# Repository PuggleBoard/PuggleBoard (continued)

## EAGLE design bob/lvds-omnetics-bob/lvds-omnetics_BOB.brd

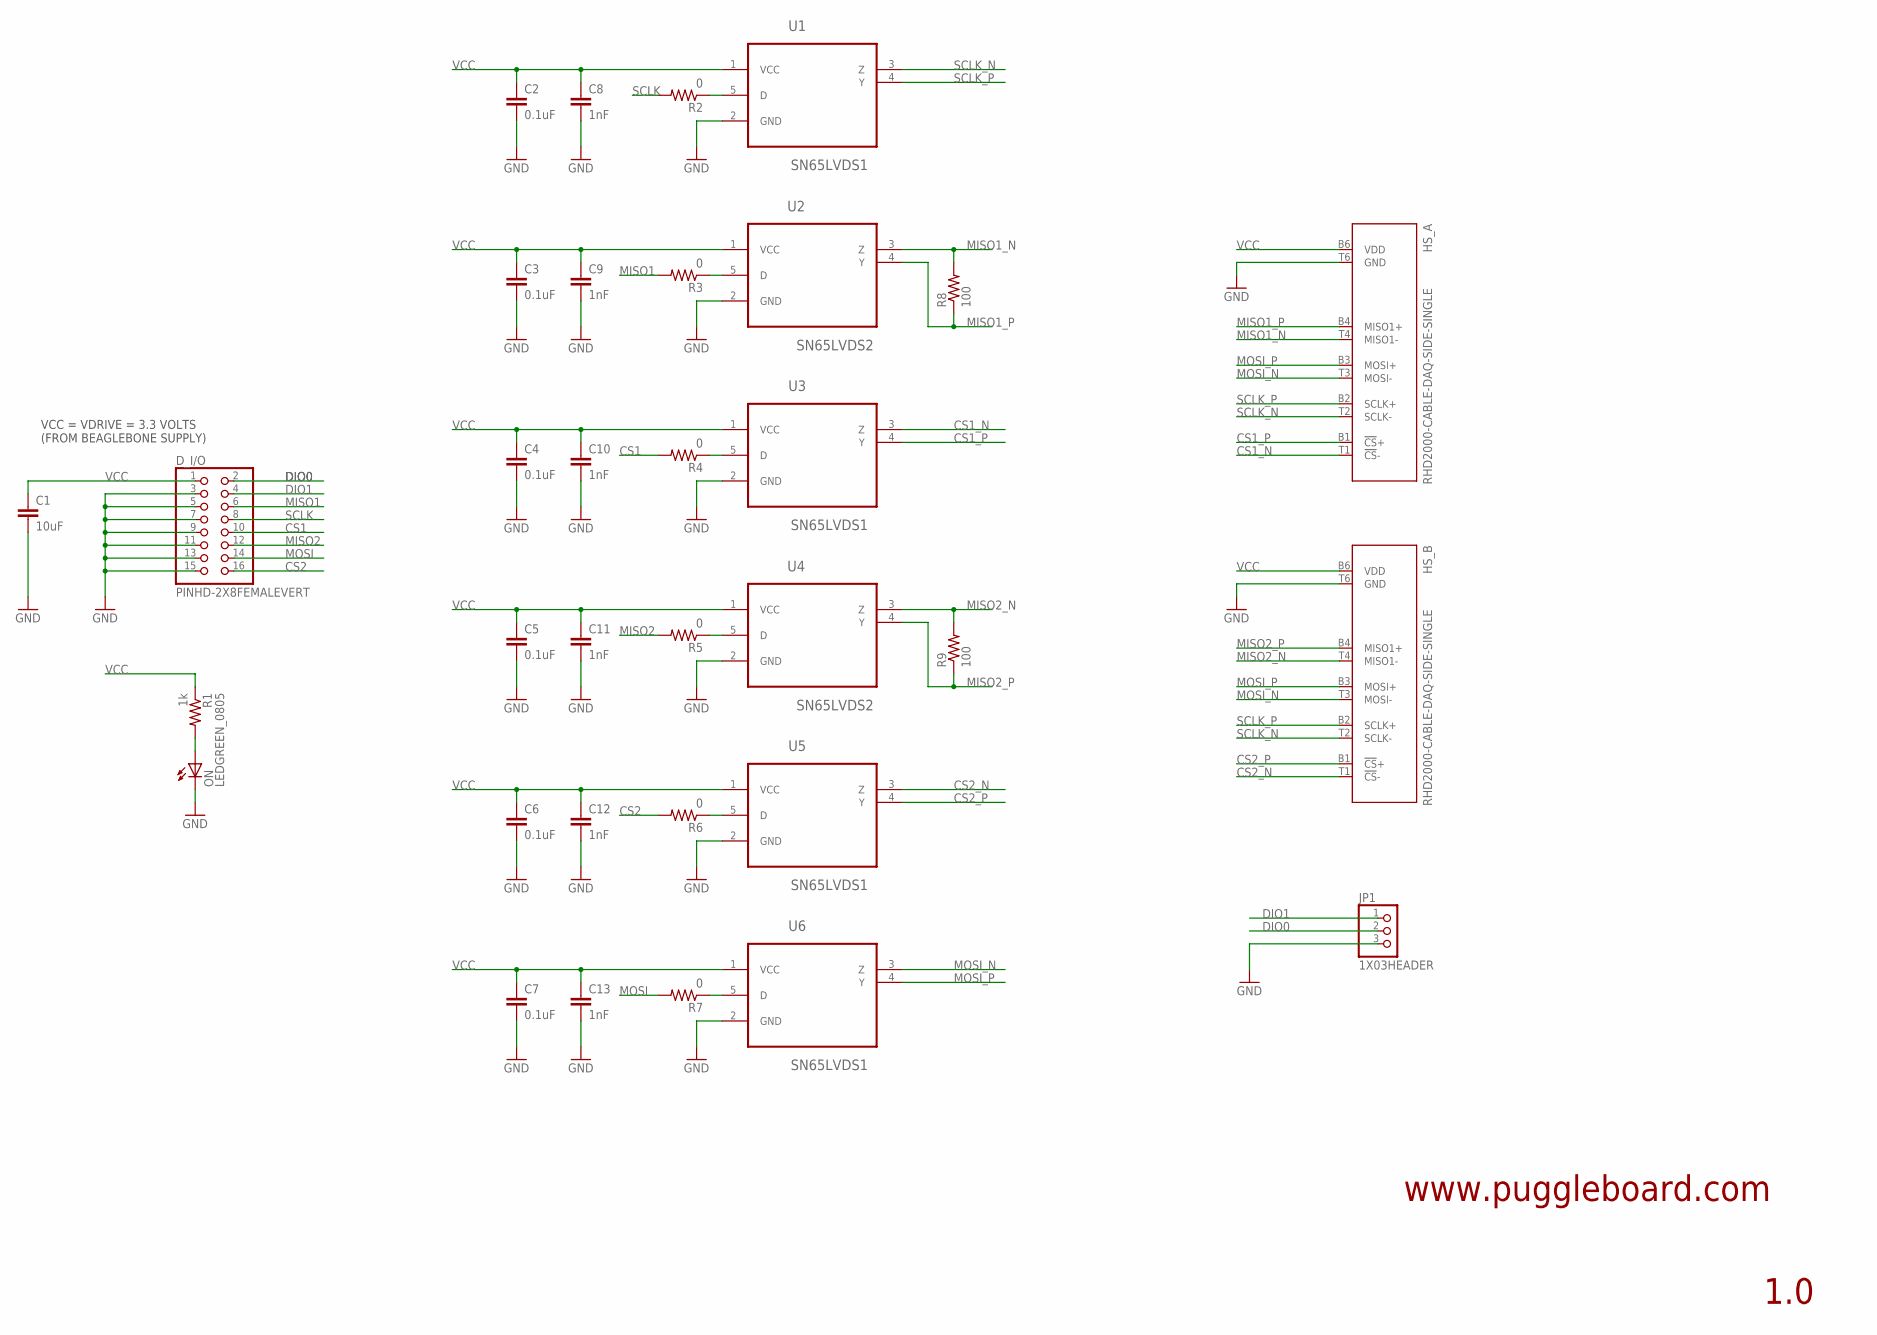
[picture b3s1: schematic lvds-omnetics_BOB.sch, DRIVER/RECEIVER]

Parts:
C1: 10uF; 0805
C2, C3, C4, C5, C6, C7: 0.1uF; 0603
C8, C9, C10, C11, C12, C13: 1nF; 0603
D_I/O: PINHD-2X8FEMALEVERT; 2X08
HS_A: RHD2000-CABLE-DAQ-SIDE-SINGLE; OMNETICS_PZN_12_AA-SINGLEBUS
HS_B: RHD2000-CABLE-DAQ-SIDE-SINGLE; OMNETICS_PZN_12_AA-SINGLEBUS
JP1: 1X03HEADER; 1X03
ON: LEDGREEN_0805; CHIP-LED0805
R1: 1k; 0603
R2, R3, R4, R5, R6, R7: 0; 0603
R8, R9: 100; 0603
U1, U3, U5, U6: SN65LVDS1; SOT95P280X145-5N; DIGIKEY 296-6919-1-ND
U2, U4: SN65LVDS2; SOT95P280X145-5N; DIGIKEY 296-6920-1-ND

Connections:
CS1: D_I/O.10, R4.2
CS1_N: HS_A.T1 (!CS!-), U3.3 (Z)
CS1_P: HS_A.B1 (!CS!+), U3.4 (Y)
CS2: D_I/O.16, R6.2
CS2_N: HS_B.T1 (!CS!-), U5.3 (Z)
CS2_P: HS_B.B1 (!CS!+), U5.4 (Y)
DIO0: D_I/O.2, JP1.2
DIO1: D_I/O.4, JP1.1
GND: C1.2, C2.2, C3.2, C4.2, C5.2, C6.2, C7.2, C8.2, C9.2, C10.2, C11.2, C12.2, C13.2, D_I/O.3, D_I/O.5, D_I/O.7, D_I/O.9, D_I/O.11, D_I/O.13, D_I/O.15, HS_A.T6 (GND), HS_B.T6 (GND), JP1.3, ON.C, U1.2 (GND), U2.2 (GND), U3.2 (GND), U4.2 (GND), U5.2 (GND), U6.2 (GND)
MISO1: D_I/O.6, R3.2
MISO1_N: HS_A.T4 (MISO1-), R8.2, U2.3 (Z)
MISO1_P: HS_A.B4 (MISO1+), R8.1, U2.4 (Y)
MISO2: D_I/O.12, R5.2
MISO2_N: HS_B.T4 (MISO1-), R9.2, U4.3 (Z)
MISO2_P: HS_B.B4 (MISO1+), R9.1, U4.4 (Y)
MOSI: D_I/O.14, R7.2
MOSI_N: HS_A.T3 (MOSI-), HS_B.T3 (MOSI-), U6.3 (Z)
MOSI_P: HS_A.B3 (MOSI+), HS_B.B3 (MOSI+), U6.4 (Y)
unnamed: R3.1, U2.5 (D)
unnamed: R4.1, U3.5 (D)
unnamed: R5.1, U4.5 (D)
unnamed: R6.1, U5.5 (D)
unnamed: R7.1, U6.5 (D)
unnamed: R2.1, U1.5 (D)
unnamed: ON.A, R1.2
SCLK: D_I/O.8, R2.2
SCLK_N: HS_A.T2 (SCLK-), HS_B.T2 (SCLK-), U1.3 (Z)
SCLK_P: HS_A.B2 (SCLK+), HS_B.B2 (SCLK+), U1.4 (Y)
VCC: C1.1, C2.1, C3.1, C4.1, C5.1, C6.1, C7.1, C8.1, C9.1, C10.1, C11.1, C12.1, C13.1, D_I/O.1, HS_A.B6 (VDD), HS_B.B6 (VDD), R1.1, U1.1 (VCC), U2.1 (VCC), U3.1 (VCC), U4.1 (VCC), U5.1 (VCC), U6.1 (VCC)

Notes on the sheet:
www.puggleboard.com
1.0
VCC = VDRIVE = 3.3 VOLTS (FROM BEAGLEBONE SUPPLY)

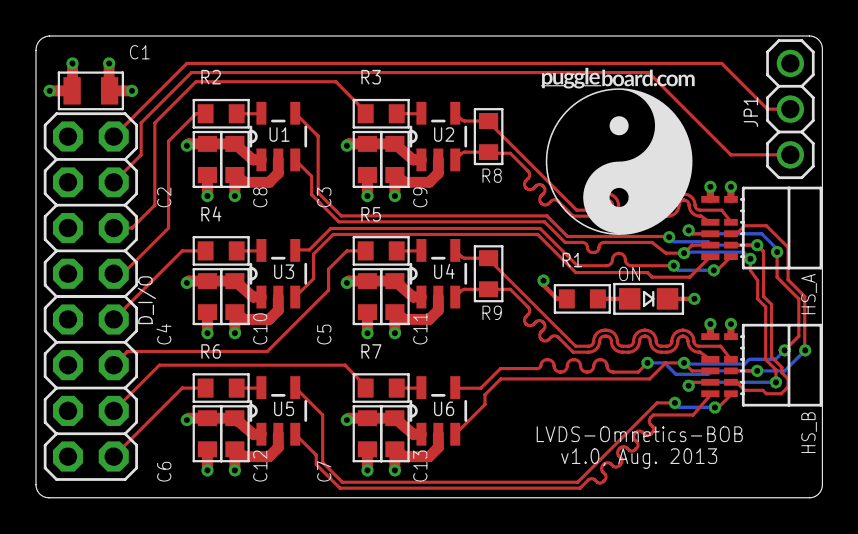
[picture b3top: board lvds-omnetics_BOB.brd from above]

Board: 4 copper layers, 43.7 x 25.7 mm, 35 parts (1 on the bottom side), 29 nets.

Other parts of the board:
U$1: PB-LOGO
U$2: OSHW_FILLX500_NOTEXT

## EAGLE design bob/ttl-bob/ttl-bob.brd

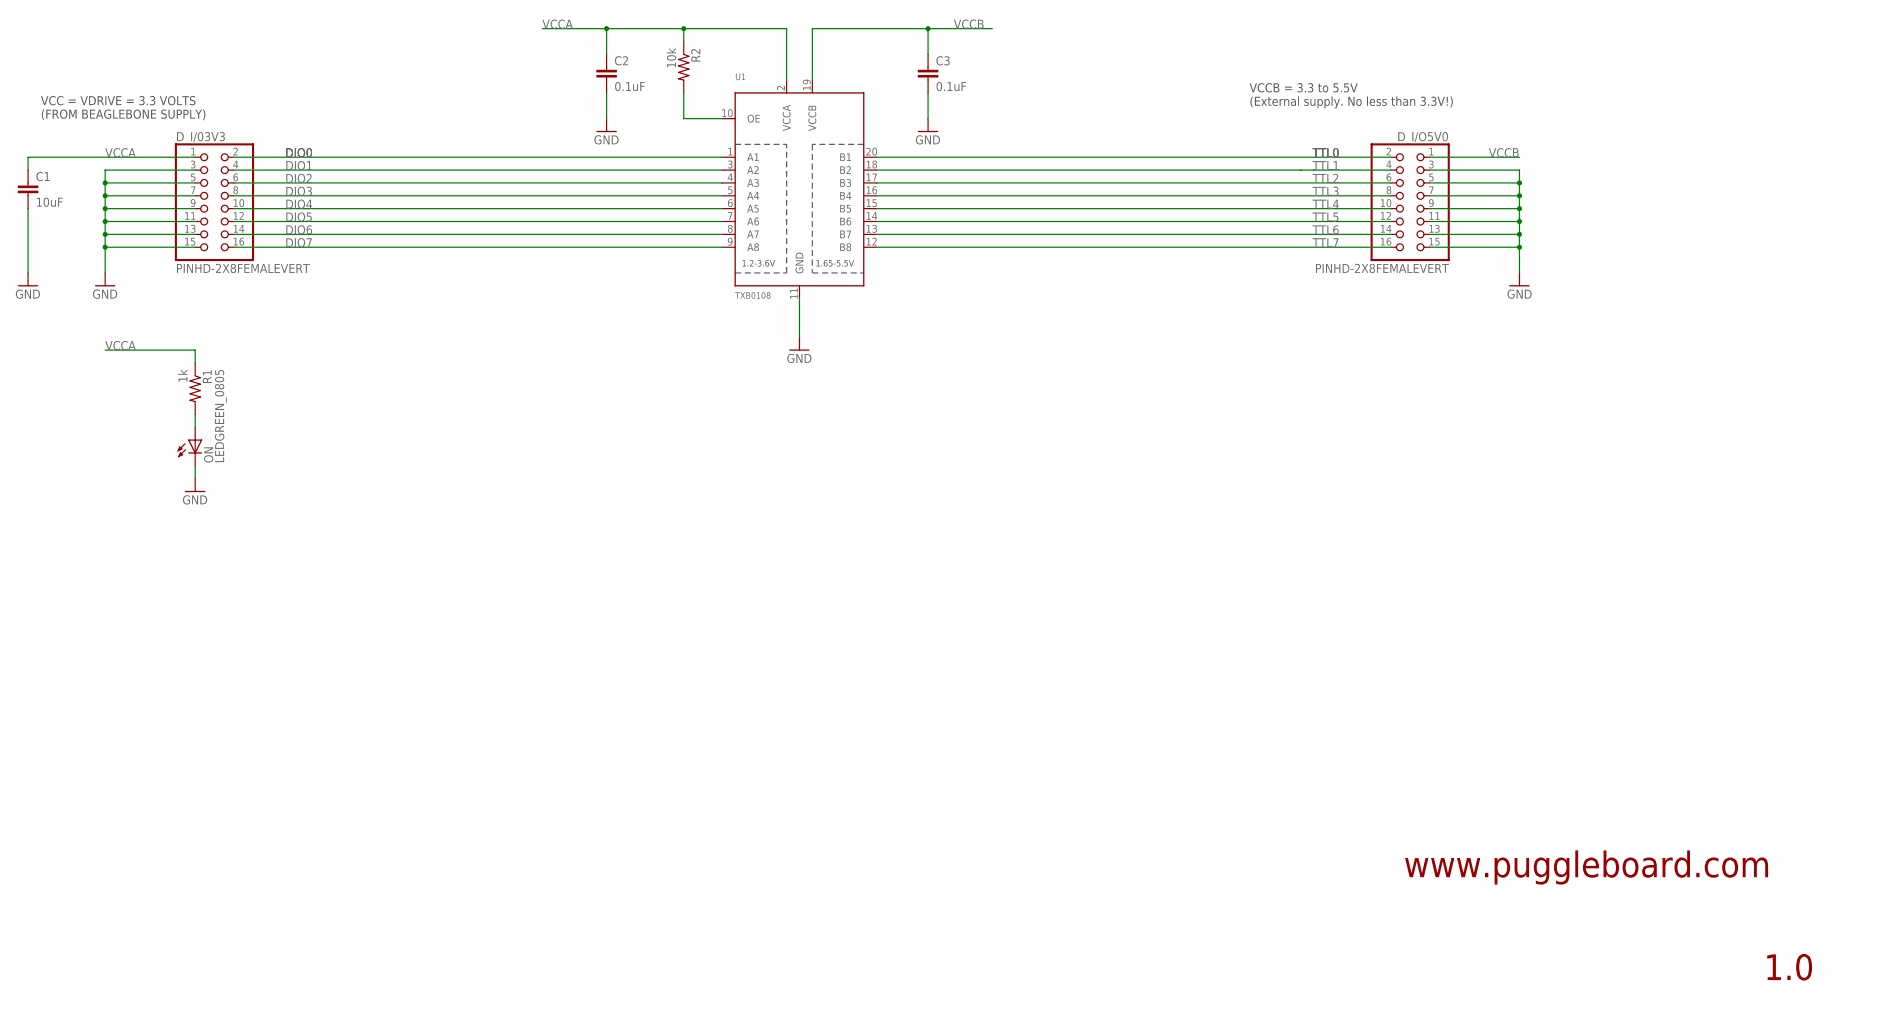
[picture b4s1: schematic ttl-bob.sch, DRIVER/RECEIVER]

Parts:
C1: 10uF; 0805
C2, C3: 0.1uF; 0603
D_I/03V3: PINHD-2X8FEMALEVERT; 2X08
D_I/O5V0: PINHD-2X8FEMALEVERT; 2X08
ON: LEDGREEN_0805; CHIP-LED0805
R1: 1k; 0603; MPN ERJ-3EKF1001V
R2: 10k; 0603; MPN ERJ-3EKF1002V
U1: TXB0108; TSSOP20

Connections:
DIO0: D_I/03V3.2, U1.1 (A1)
DIO1: D_I/03V3.4, U1.3 (A2)
DIO2: D_I/03V3.6, U1.4 (A3)
DIO3: D_I/03V3.8, U1.5 (A4)
DIO4: D_I/03V3.10, U1.6 (A5)
DIO5: D_I/03V3.12, U1.7 (A6)
DIO6: D_I/03V3.14, U1.8 (A7)
DIO7: D_I/03V3.16, U1.9 (A8)
GND: C1.2, C2.2, C3.2, D_I/03V3.3, D_I/03V3.5, D_I/03V3.7, D_I/03V3.9, D_I/03V3.11, D_I/03V3.13, D_I/03V3.15, D_I/O5V0.3, D_I/O5V0.5, D_I/O5V0.7, D_I/O5V0.9, D_I/O5V0.11, D_I/O5V0.13, D_I/O5V0.15, ON.C, U1.11 (GND)
unnamed: R2.2, U1.10 (OE)
unnamed: ON.A, R1.2
TTL0: D_I/O5V0.2, U1.20 (B1)
TTL1: D_I/O5V0.4, U1.18 (B2)
TTL2: D_I/O5V0.6, U1.17 (B3)
TTL3: D_I/O5V0.8, U1.16 (B4)
TTL4: D_I/O5V0.10, U1.15 (B5)
TTL5: D_I/O5V0.12, U1.14 (B6)
TTL6: D_I/O5V0.14, U1.13 (B7)
TTL7: D_I/O5V0.16, U1.12 (B8)
VCCA: C1.1, C2.1, D_I/03V3.1, R1.1, R2.1, U1.2 (VCCA)
VCCB: C3.1, D_I/O5V0.1, U1.19 (VCCB)

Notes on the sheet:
www.puggleboard.com
1.0
VCC = VDRIVE = 3.3 VOLTS (FROM BEAGLEBONE SUPPLY)
VCCB = 3.3 to 5.5V (External supply. No less than 3.3V!)

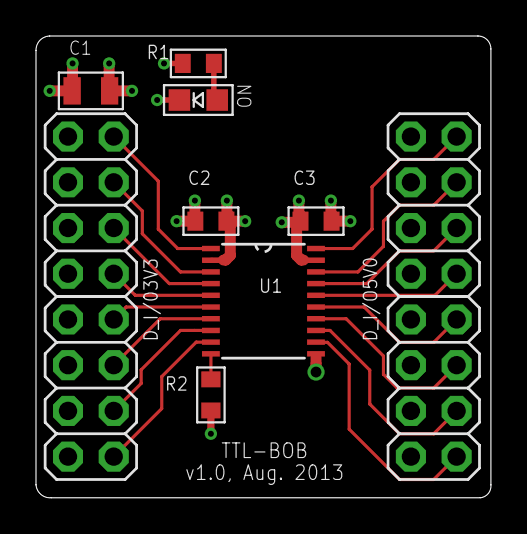
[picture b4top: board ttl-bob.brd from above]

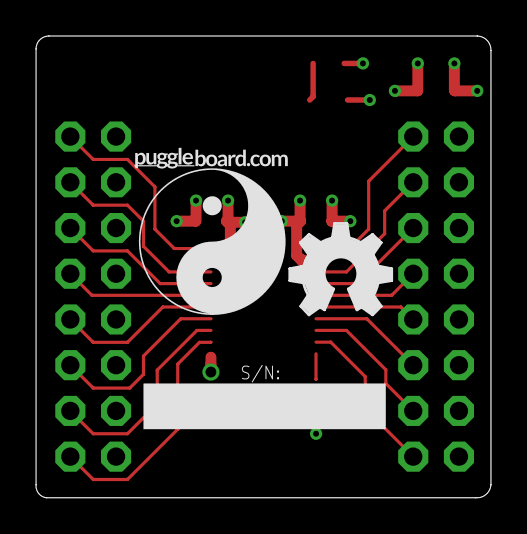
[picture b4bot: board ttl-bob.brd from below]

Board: 4 copper layers, 25.3 x 25.7 mm, 11 parts (2 on the bottom side), 21 nets.

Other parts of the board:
U$1: PB-LOGO
U$2: OSHW_FILLX200_NOTEXT

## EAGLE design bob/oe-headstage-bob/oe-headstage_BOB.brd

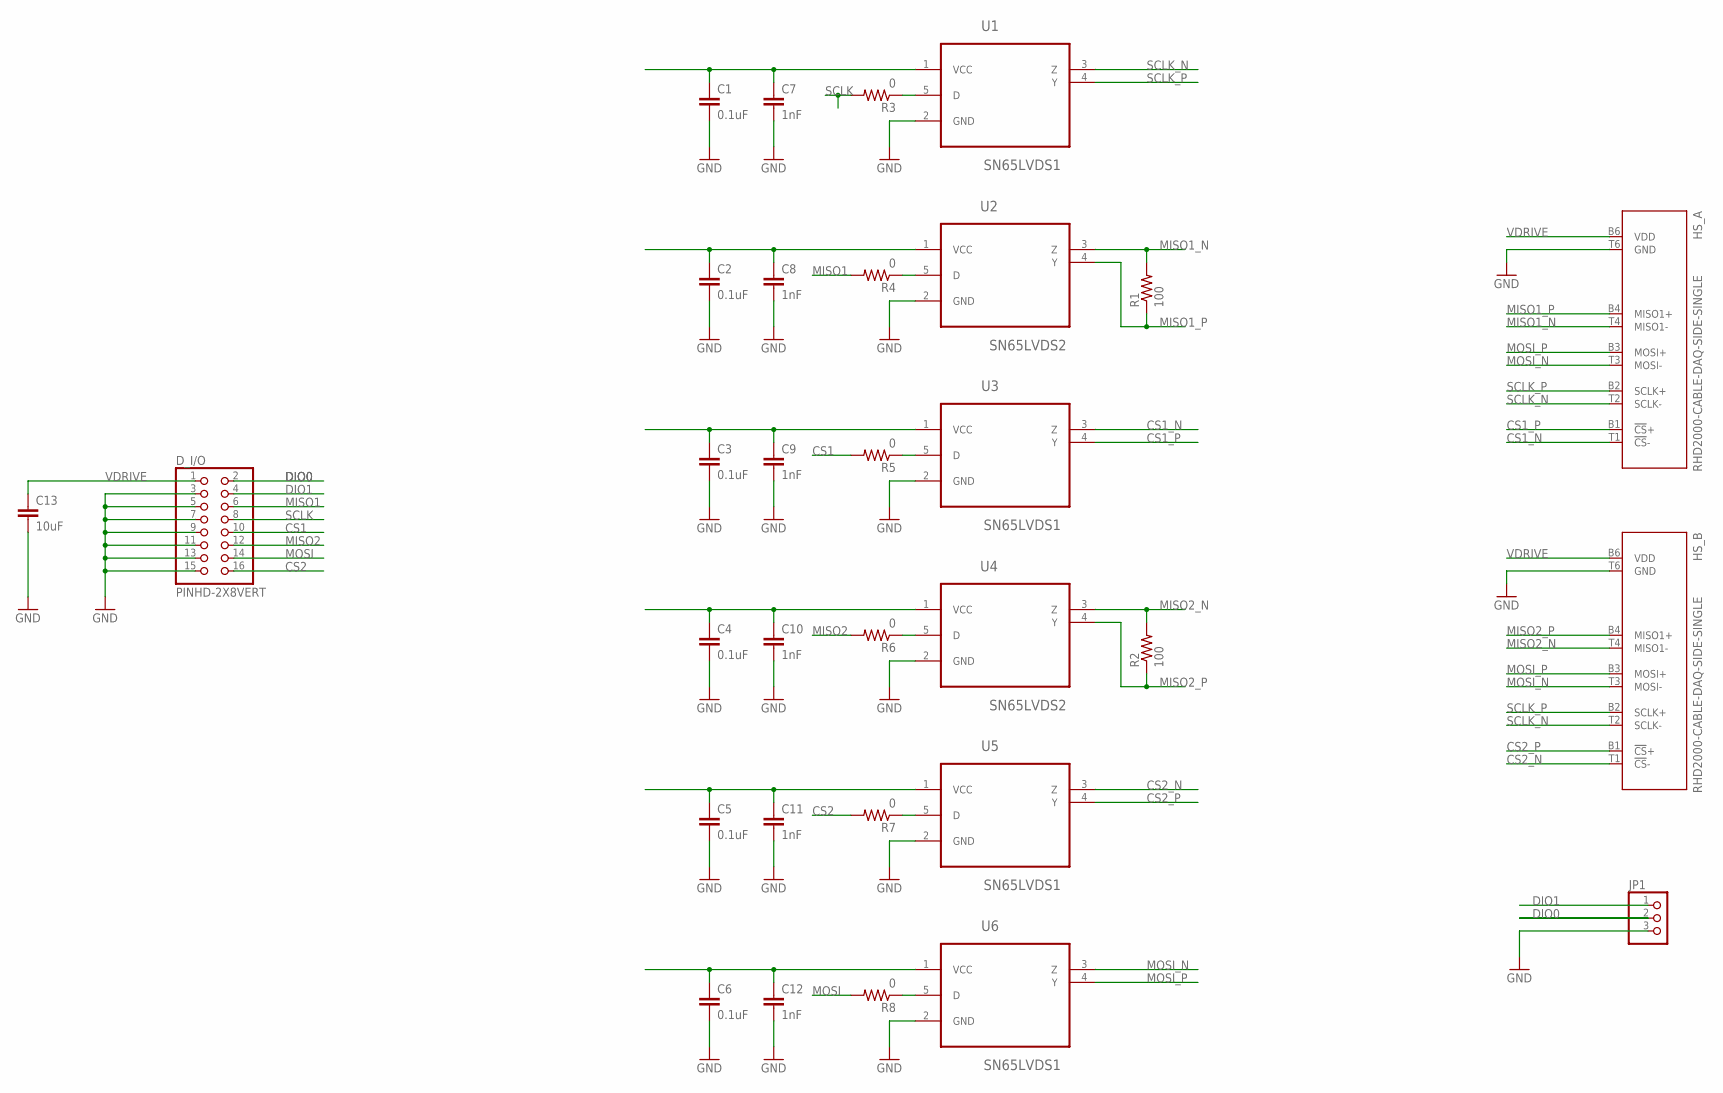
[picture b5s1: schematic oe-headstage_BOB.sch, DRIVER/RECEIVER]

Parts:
C1, C2, C3, C4, C5, C6: 0.1uF; 0603
C7, C8, C9, C10, C11, C12: 1nF; 0603
C13: 10uF; 0805
D_I/O: PINHD-2X8VERT; 2X08
HS_A: RHD2000-CABLE-DAQ-SIDE-SINGLE; OMNETICS_PZN_12_AA-SINGLEBUS
HS_B: RHD2000-CABLE-DAQ-SIDE-SINGLE; OMNETICS_PZN_12_AA-SINGLEBUS
JP1: PINHD-1X3; 1X03
R1, R2: 100; 0603
R3, R4, R5, R6, R7, R8: 0; 0603
U1, U3, U5, U6: SN65LVDS1; SOT95P280X145-5N; DIGIKEY 296-6919-1-ND
U2, U4: SN65LVDS2; SOT95P280X145-5N; DIGIKEY 296-6920-1-ND

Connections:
CS1: D_I/O.10, R5.2
CS1_N: HS_A.T1 (!CS!-), U3.3 (Z)
CS1_P: HS_A.B1 (!CS!+), U3.4 (Y)
CS2: D_I/O.16, R7.2
CS2_N: HS_B.T1 (!CS!-), U5.3 (Z)
CS2_P: HS_B.B1 (!CS!+), U5.4 (Y)
DIO0: D_I/O.2, JP1.2
DIO1: D_I/O.4, JP1.1
GND: C1.2, C2.2, C3.2, C4.2, C5.2, C6.2, C7.2, C8.2, C9.2, C10.2, C11.2, C12.2, C13.2, D_I/O.3, D_I/O.5, D_I/O.7, D_I/O.9, D_I/O.11, D_I/O.13, D_I/O.15, HS_A.T6 (GND), HS_B.T6 (GND), JP1.3, U1.2 (GND), U2.2 (GND), U3.2 (GND), U4.2 (GND), U5.2 (GND), U6.2 (GND)
MISO1: D_I/O.6, R4.2
MISO1_N: HS_A.T4 (MISO1-), R1.2, U2.3 (Z)
MISO1_P: HS_A.B4 (MISO1+), R1.1, U2.4 (Y)
MISO2: D_I/O.12, R6.2
MISO2_N: HS_B.T4 (MISO1-), R2.2, U4.3 (Z)
MISO2_P: HS_B.B4 (MISO1+), R2.1, U4.4 (Y)
MOSI: D_I/O.14, R8.2
MOSI_N: HS_A.T3 (MOSI-), HS_B.T3 (MOSI-), U6.3 (Z)
MOSI_P: HS_A.B3 (MOSI+), HS_B.B3 (MOSI+), U6.4 (Y)
unnamed: R4.1, U2.5 (D)
unnamed: R5.1, U3.5 (D)
unnamed: R6.1, U4.5 (D)
unnamed: R7.1, U5.5 (D)
unnamed: R8.1, U6.5 (D)
unnamed: R3.1, U1.5 (D)
SCLK: D_I/O.8, R3.2
SCLK_N: HS_A.T2 (SCLK-), HS_B.T2 (SCLK-), U1.3 (Z)
SCLK_P: HS_A.B2 (SCLK+), HS_B.B2 (SCLK+), U1.4 (Y)
VDRIVE: C1.1, C2.1, C3.1, C4.1, C5.1, C6.1, C7.1, C8.1, C9.1, C10.1, C11.1, C12.1, C13.1, D_I/O.1, HS_A.B6 (VDD), HS_B.B6 (VDD), U1.1 (VCC), U2.1 (VCC), U3.1 (VCC), U4.1 (VCC), U5.1 (VCC), U6.1 (VCC)

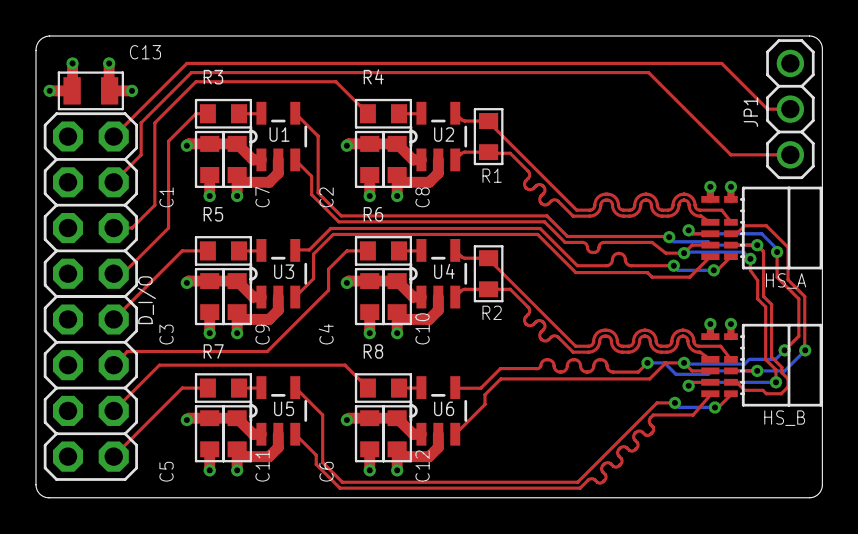
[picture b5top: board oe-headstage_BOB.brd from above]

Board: 4 copper layers, 43.7 x 25.7 mm, 31 parts (0 on the bottom side), 28 nets.

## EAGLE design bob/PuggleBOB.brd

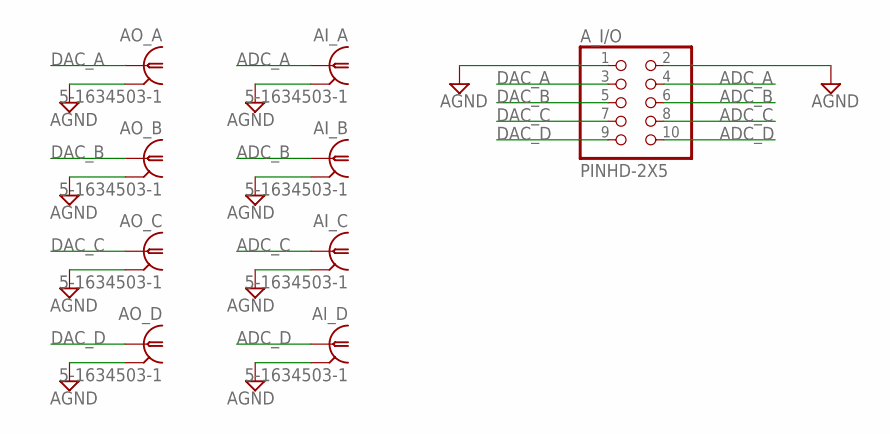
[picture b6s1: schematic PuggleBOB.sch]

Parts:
AI_A: 5-1634503-1; B35N61
AI_B: 5-1634503-1; B35N61
AI_C: 5-1634503-1; B35N61
AI_D: 5-1634503-1; B35N61
AO_A: 5-1634503-1; B35N61
AO_B: 5-1634503-1; B35N61
AO_C: 5-1634503-1; B35N61
AO_D: 5-1634503-1; B35N61
A_I/O: PINHD-2X5; 2X05

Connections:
ADC_A: AI_A.1, A_I/O.4
ADC_B: AI_B.1, A_I/O.6
ADC_C: AI_C.1, A_I/O.8
ADC_D: AI_D.1, A_I/O.10
AGND: AI_A.2, AI_A.3 (2), AI_A.4 (2), AI_A.5 (2), AI_B.2, AI_B.3 (2), AI_B.4 (2), AI_B.5 (2), AI_C.2, AI_C.3 (2), AI_C.4 (2), AI_C.5 (2), AI_D.2, AI_D.3 (2), AI_D.4 (2), AI_D.5 (2), AO_A.2, AO_A.3 (2), AO_A.4 (2), AO_A.5 (2), AO_B.2, AO_B.3 (2), AO_B.4 (2), AO_B.5 (2), AO_C.2, AO_C.3 (2), AO_C.4 (2), AO_C.5 (2), AO_D.2, AO_D.3 (2), AO_D.4 (2), AO_D.5 (2), A_I/O.1, A_I/O.2
DAC_A: AO_A.1, A_I/O.3
DAC_B: AO_B.1, A_I/O.5
DAC_C: AO_C.1, A_I/O.7
DAC_D: AO_D.1, A_I/O.9

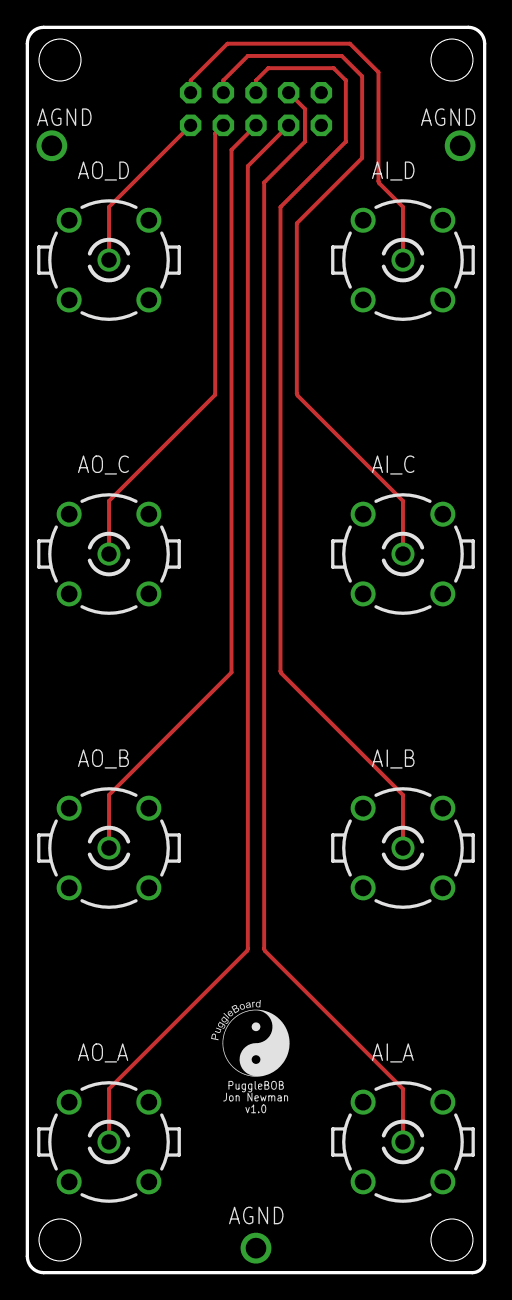
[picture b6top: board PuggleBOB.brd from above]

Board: 2 copper layers, 35.6 x 96.8 mm, 9 parts (1 on the bottom side), 9 nets.

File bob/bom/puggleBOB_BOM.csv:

Part,Value,Device,Package,Description,MPN,DKPN
AI_0,5-1634503-1,BN35N61,B35N61,BNC CONNECTOR,5-1634503-1,A97581-ND
AI_1,5-1634503-1,BN35N61,B35N61,BNC CONNECTOR,5-1634503-1,A97581-ND
AI_2,5-1634503-1,BN35N61,B35N61,BNC CONNECTOR,5-1634503-1,A97581-ND
AI_3,5-1634503-1,BN35N61,B35N61,BNC CONNECTOR,5-1634503-1,A97581-ND
AO_0,5-1634503-1,BN35N61,B35N61,BNC CONNECTOR,5-1634503-1,A97581-ND
AO_1,5-1634503-1,BN35N61,B35N61,BNC CONNECTOR,5-1634503-1,A97581-ND
AO_2,5-1634503-1,BN35N61,B35N61,BNC CONNECTOR,5-1634503-1,A97581-ND
AO_3,5-1634503-1,BN35N61,B35N61,BNC CONNECTOR,5-1634503-1,A97581-ND
A_I/O,PINHD-2X5/90,PINHD-2X5/90,2X05/90,"0.1 Inch pitch, 2-row, male header",1-1634688-0,A104906-ND

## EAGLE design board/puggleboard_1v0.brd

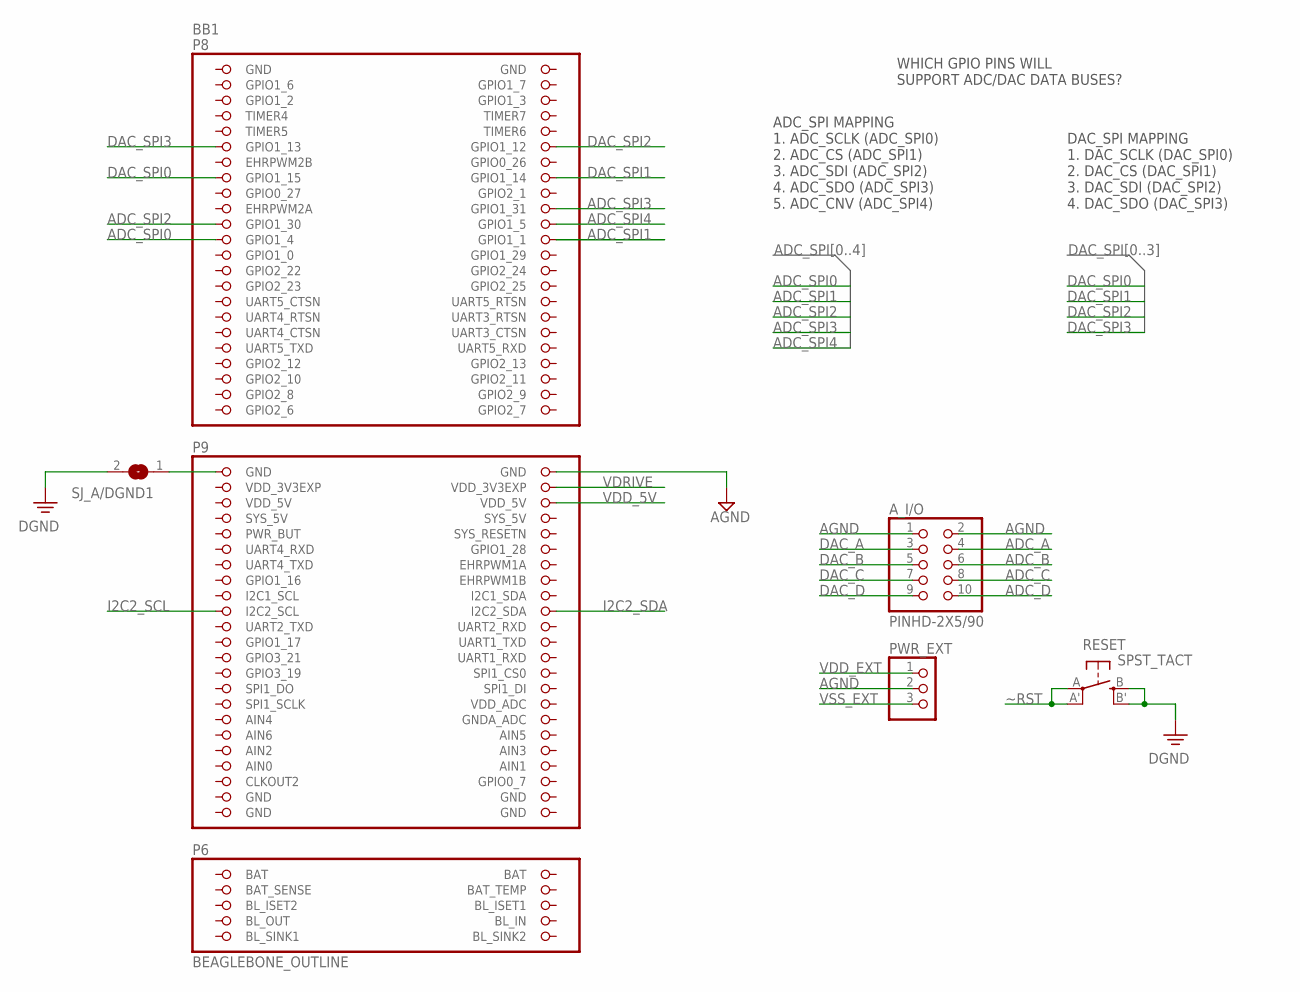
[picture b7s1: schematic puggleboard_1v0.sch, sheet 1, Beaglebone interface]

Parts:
A_I/O: PINHD-2X5/90; 2X05/90
BB1: BEAGLEBONE_OUTLINE; BEAGLEBONE_SHIELD
PWR_EXT: PINHD-1X3; 1X03
RESET: SPST_TACT; EVQ-Q2-A
SJ_A/DGND1: SJ

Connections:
ADC_A: A_I/O.4; also elsewhere on the board
ADC_B: A_I/O.6; also elsewhere on the board
ADC_C: A_I/O.8; also elsewhere on the board
ADC_D: A_I/O.10; also elsewhere on the board
ADC_SPI0: BB1.23 (GPIO1_4); also elsewhere on the board
ADC_SPI1: BB1.24 (GPIO1_1); also elsewhere on the board
ADC_SPI2: BB1.21 (GPIO1_30); also elsewhere on the board
ADC_SPI3: BB1.20 (GPIO1_31); also elsewhere on the board
ADC_SPI4: BB1.22 (GPIO1_5); also elsewhere on the board
AGND: A_I/O.1, A_I/O.2, BB1.48 (GND), PWR_EXT.2; also elsewhere on the board
AIN0: BB1.85 (AIN0)
BAT_SENSE: BB1.95 (BAT_SENSE)
BL_IN: BB1.97 (BL_IN)
BL_OUT: BB1.100 (BL_OUT)
BL_SINK1: BB1.101 (BL_SINK1)
BL_SINK2: BB1.102 (BL_SINK2)
DAC_A: A_I/O.3; also elsewhere on the board
DAC_B: A_I/O.5; also elsewhere on the board
DAC_C: A_I/O.7; also elsewhere on the board
DAC_D: A_I/O.9; also elsewhere on the board
DAC_SPI0: BB1.15 (GPIO1_15); also elsewhere on the board
DAC_SPI1: BB1.16 (GPIO1_14); also elsewhere on the board
DAC_SPI2: BB1.12 (GPIO1_12); also elsewhere on the board
DAC_SPI3: BB1.11 (GPIO1_13); also elsewhere on the board
DGND: RESET.B (S), RESET.B' (S1), SJ_A/DGND1.2; also elsewhere on the board
GND: BB1.1 (GND), BB1.2 (GND), BB1.89 (GND), BB1.90 (GND), BB1.91 (GND), BB1.92 (GND)
I2C2_SCL: BB1.65 (I2C2_SCL); also elsewhere on the board
I2C2_SDA: BB1.66 (I2C2_SDA); also elsewhere on the board
unnamed: BB1.47 (GND), SJ_A/DGND1.1
SYS_5V: BB1.53 (SYS_5V)
VDD_3V3EXP: BB1.49 (VDD_3V3EXP)
VDD_5V: BB1.51 (VDD_5V), BB1.52 (VDD_5V); also elsewhere on the board
VDD_EXT: PWR_EXT.1; also elsewhere on the board
VDRIVE: BB1.50 (VDD_3V3EXP); also elsewhere on the board
VSS_EXT: PWR_EXT.3; also elsewhere on the board
~RST: RESET.A, RESET.A' (P1); also elsewhere on the board

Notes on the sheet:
ADC_SPI MAPPING 1. ADC_SCLK (ADC_SPI0) 2. ADC_CS (ADC_SPI1) 3. ADC_SDI (ADC_SPI2) 4. ADC_SDO (ADC_SPI3) 5. ADC_CNV (ADC_SPI4)
DAC_SPI MAPPING 1. DAC_SCLK (DAC_SPI0) 2. DAC_CS (DAC_SPI1) 3. DAC_SDI (DAC_SPI2) 4. DAC_SDO (DAC_SPI3)
WHICH GPIO PINS WILL SUPPORT ADC/DAC DATA BUSES?

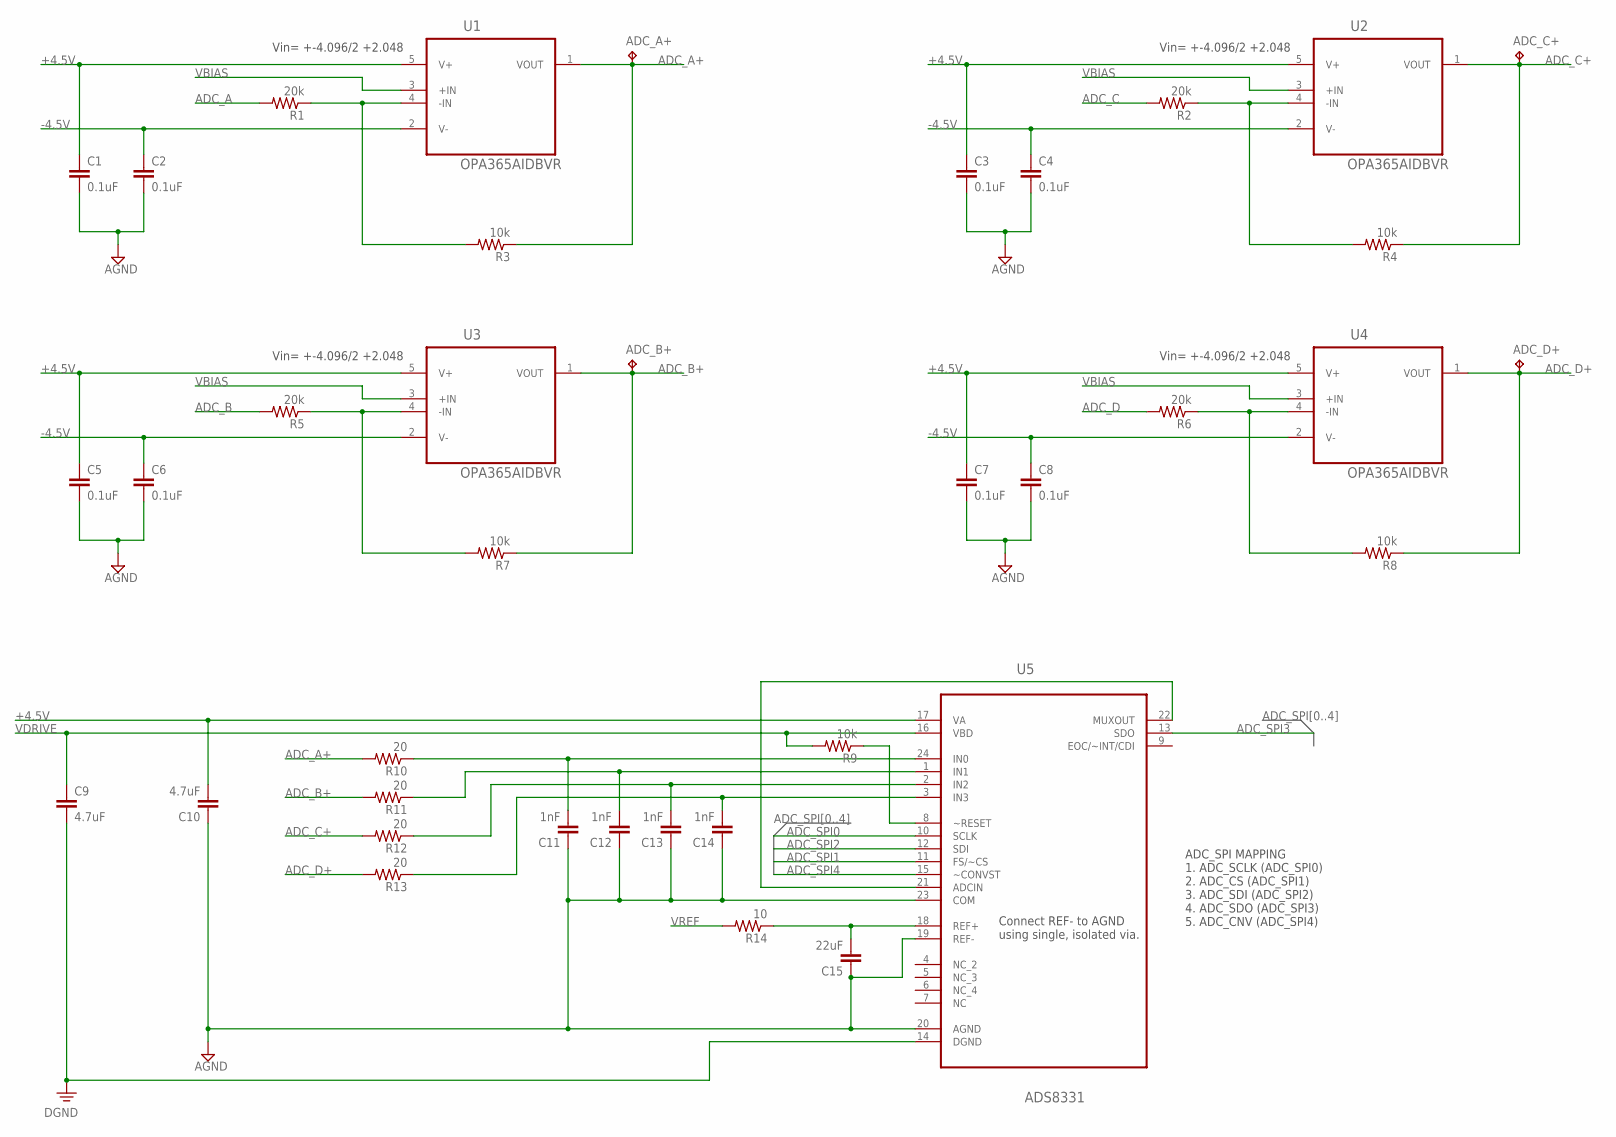
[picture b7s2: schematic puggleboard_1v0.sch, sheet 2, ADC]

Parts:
ADC_A+: TPB1,27; B1,27
ADC_B+: TPB1,27; B1,27
ADC_C+: TPB1,27; B1,27
ADC_D+: TPB1,27; B1,27
C1, C2, C3, C4, C5, C6, C7, C8: 0.1uF; C0603
C9, C10: 4.7uF; C0805
C11, C12, C13, C14: 1nF; C0603
C15: 22uF; C0603
R1, R2, R5, R6: 20k; R0603
R3, R4, R7, R8, R9: 10k; R0603
R10, R11, R12, R13: 20; R0603
R14: 10; R0603
U1, U2, U3, U4: OPA365AIDBVR; SOT95P280X145-5N
U5: ADS8331; SOP65P640X120-24N

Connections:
+4.5V: C1.1, C3.1, C5.1, C7.1, C10.2, U1.5 (V+), U2.5 (V+), U3.5 (V+), U4.5 (V+), U5.17 (VA); also elsewhere on the board
-4.5V: C2.1, C4.1, C6.1, C8.1, U1.2 (V-), U2.2 (V-), U3.2 (V-), U4.2 (V-); also elsewhere on the board
ADC_A: R1.2; also elsewhere on the board
ADC_A+: ADC_A+.TP, R3.1, R10.2, U1.1 (VOUT)
ADC_B: R5.2; also elsewhere on the board
ADC_B+: ADC_B+.TP, R7.1, R11.2, U3.1 (VOUT)
ADC_C: R2.2; also elsewhere on the board
ADC_C+: ADC_C+.TP, R4.1, R12.2, U2.1 (VOUT)
ADC_D: R6.2; also elsewhere on the board
ADC_D+: ADC_D+.TP, R8.1, R13.2, U4.1 (VOUT)
ADC_SPI0: U5.10 (SCLK); also elsewhere on the board
ADC_SPI1: U5.11 (FS/~CS); also elsewhere on the board
ADC_SPI2: U5.12 (SDI); also elsewhere on the board
ADC_SPI3: U5.13 (SDO); also elsewhere on the board
ADC_SPI4: U5.15 (~CONVST); also elsewhere on the board
AGND: C1.2, C2.2, C3.2, C4.2, C5.2, C6.2, C7.2, C8.2, C10.1, C11.1, C12.1, C13.1, C14.1, C15.1, U5.19 (REF-), U5.20 (AGND), U5.23 (COM); also elsewhere on the board
DGND: C9.2, U5.14 (DGND); also elsewhere on the board
unnamed: R1.1, R3.2, U1.4 (-IN)
unnamed: R5.1, R7.2, U3.4 (-IN)
unnamed: R2.1, R4.2, U2.4 (-IN)
unnamed: R6.1, R8.2, U4.4 (-IN)
unnamed: C15.2, R14.1, U5.18 (REF+)
unnamed: U5.21 (ADCIN), U5.22 (MUXOUT)
unnamed: C11.2, R10.1, U5.24 (IN0)
unnamed: C12.2, R11.1, U5.1 (IN1)
unnamed: C13.2, R12.1, U5.2 (IN2)
unnamed: C14.2, R13.1, U5.3 (IN3)
VBIAS: U1.3 (+IN), U2.3 (+IN), U3.3 (+IN), U4.3 (+IN); also elsewhere on the board
VDRIVE: C9.1, R9.2, U5.16 (VBD); also elsewhere on the board
VREF: R14.2; also elsewhere on the board
~RST: R9.1, U5.8 (~RESET); also elsewhere on the board

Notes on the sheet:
Connect REF- to AGND using single, isolated via.
Vin= +-4.096/2 +2.048
ADC_SPI MAPPING 1. ADC_SCLK (ADC_SPI0) 2. ADC_CS (ADC_SPI1) 3. ADC_SDI (ADC_SPI2) 4. ADC_SDO (ADC_SPI3) 5. ADC_CNV (ADC_SPI4)

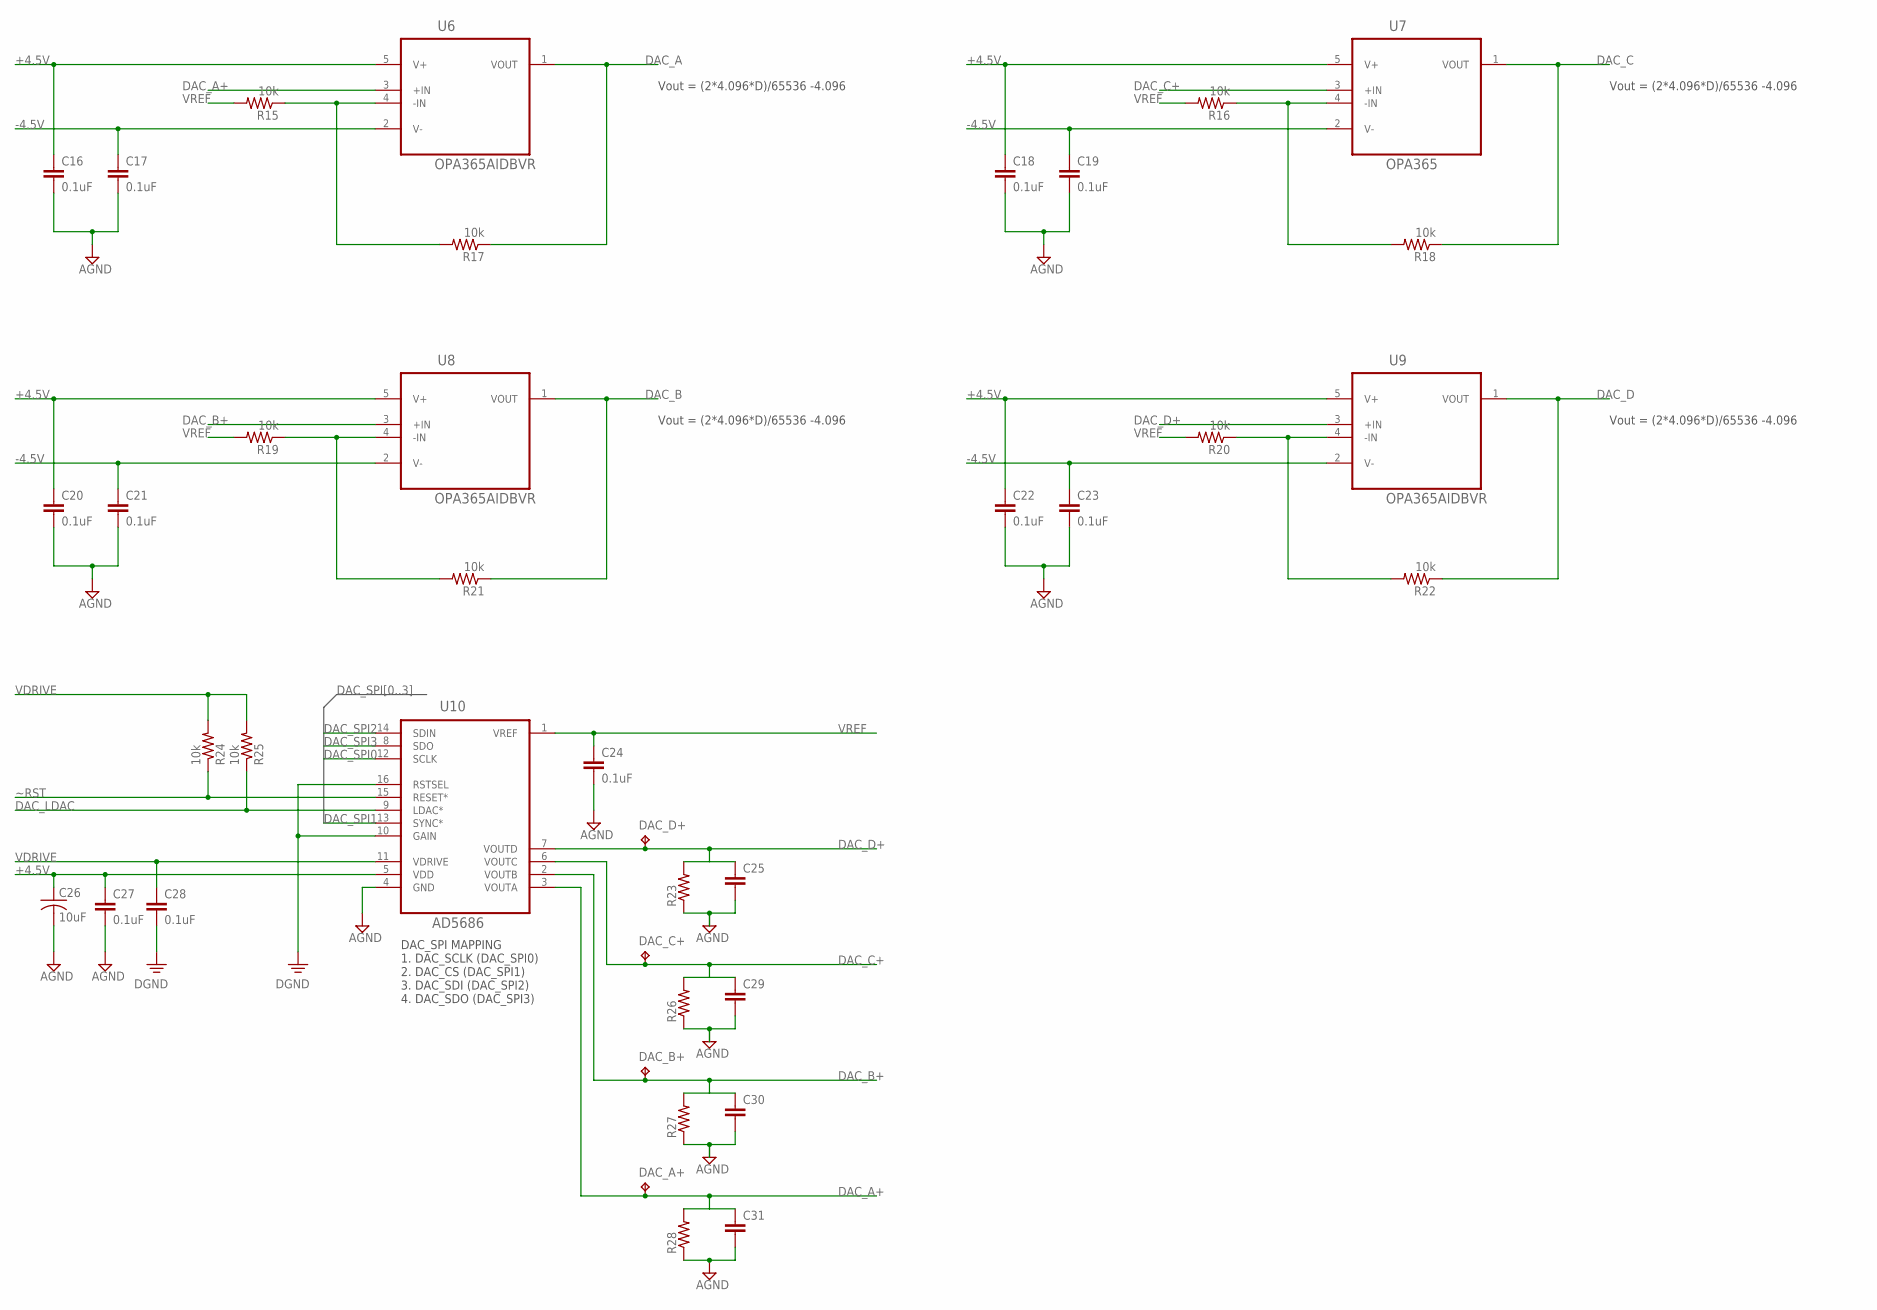
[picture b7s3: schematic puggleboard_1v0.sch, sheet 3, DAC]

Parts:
C16, C17, C18, C19, C20, C21, C22, C23, C24, C27, C28: 0.1uF; C0603
C25, C29, C30, C31: C-EUC0603; C0603
C26: 10uF; C0805
DAC_A+: TPB1,27; B1,27
DAC_B+: TPB1,27; B1,27
DAC_C+: TPB1,27; B1,27
DAC_D+: TPB1,27; B1,27
R15, R16, R17, R18, R19, R20, R21, R22, R24, R25: 10k; R0603
R23, R26, R27, R28: R-US_R0603; R0603
U6, U8, U9: OPA365AIDBVR; SOT95P280X145-5N
U7: OPA365; SOT95P280X145-5N
U10: AD5686; MO-153-AB

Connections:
+4.5V: C16.1, C18.1, C20.1, C22.1, C26.1, C27.1, U6.5 (V+), U7.5 (V+), U8.5 (V+), U9.5 (V+), U10.5 (VDD); also elsewhere on the board
-4.5V: C17.1, C19.1, C21.1, C23.1, U6.2 (V-), U7.2 (V-), U8.2 (V-), U9.2 (V-); also elsewhere on the board
AGND: C16.2, C17.2, C18.2, C19.2, C20.2, C21.2, C22.2, C23.2, C24.2, C25.2, C26.2, C27.2, C29.2, C30.2, C31.2, R23.1, R26.1, R27.1, R28.1, U10.4 (GND); also elsewhere on the board
DAC_A: R17.1, U6.1 (VOUT); also elsewhere on the board
DAC_A+: C31.1, DAC_A+.TP, R28.2, U6.3 (+IN), U10.3 (VOUTA)
DAC_B: R21.1, U8.1 (VOUT); also elsewhere on the board
DAC_B+: C30.1, DAC_B+.TP, R27.2, U8.3 (+IN), U10.2 (VOUTB)
DAC_C: R18.1, U7.1 (VOUT); also elsewhere on the board
DAC_C+: C29.1, DAC_C+.TP, R26.2, U7.3 (+IN), U10.6 (VOUTC)
DAC_D: R22.1, U9.1 (VOUT); also elsewhere on the board
DAC_D+: C25.1, DAC_D+.TP, R23.2, U9.3 (+IN), U10.7 (VOUTD)
DAC_LDAC: R25.1, U10.9 (LDAC*)
DAC_SPI0: U10.12 (SCLK); also elsewhere on the board
DAC_SPI1: U10.13 (SYNC*); also elsewhere on the board
DAC_SPI2: U10.14 (SDIN); also elsewhere on the board
DAC_SPI3: U10.8 (SDO); also elsewhere on the board
DGND: C28.2, U10.10 (GAIN), U10.16 (RSTSEL); also elsewhere on the board
unnamed: R16.1, R18.2, U7.4 (-IN)
unnamed: R19.1, R21.2, U8.4 (-IN)
unnamed: R20.1, R22.2, U9.4 (-IN)
unnamed: R15.1, R17.2, U6.4 (-IN)
VDRIVE: C28.1, R24.2, R25.2, U10.11 (VDRIVE); also elsewhere on the board
VREF: C24.1, R15.2, R16.2, R19.2, R20.2, U10.1 (VREF); also elsewhere on the board
~RST: R24.1, U10.15 (RESET*); also elsewhere on the board

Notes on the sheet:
Vout = (2*4.096*D)/65536 -4.096
DAC_SPI MAPPING 1. DAC_SCLK (DAC_SPI0) 2. DAC_CS (DAC_SPI1) 3. DAC_SDI (DAC_SPI2) 4. DAC_SDO (DAC_SPI3)
